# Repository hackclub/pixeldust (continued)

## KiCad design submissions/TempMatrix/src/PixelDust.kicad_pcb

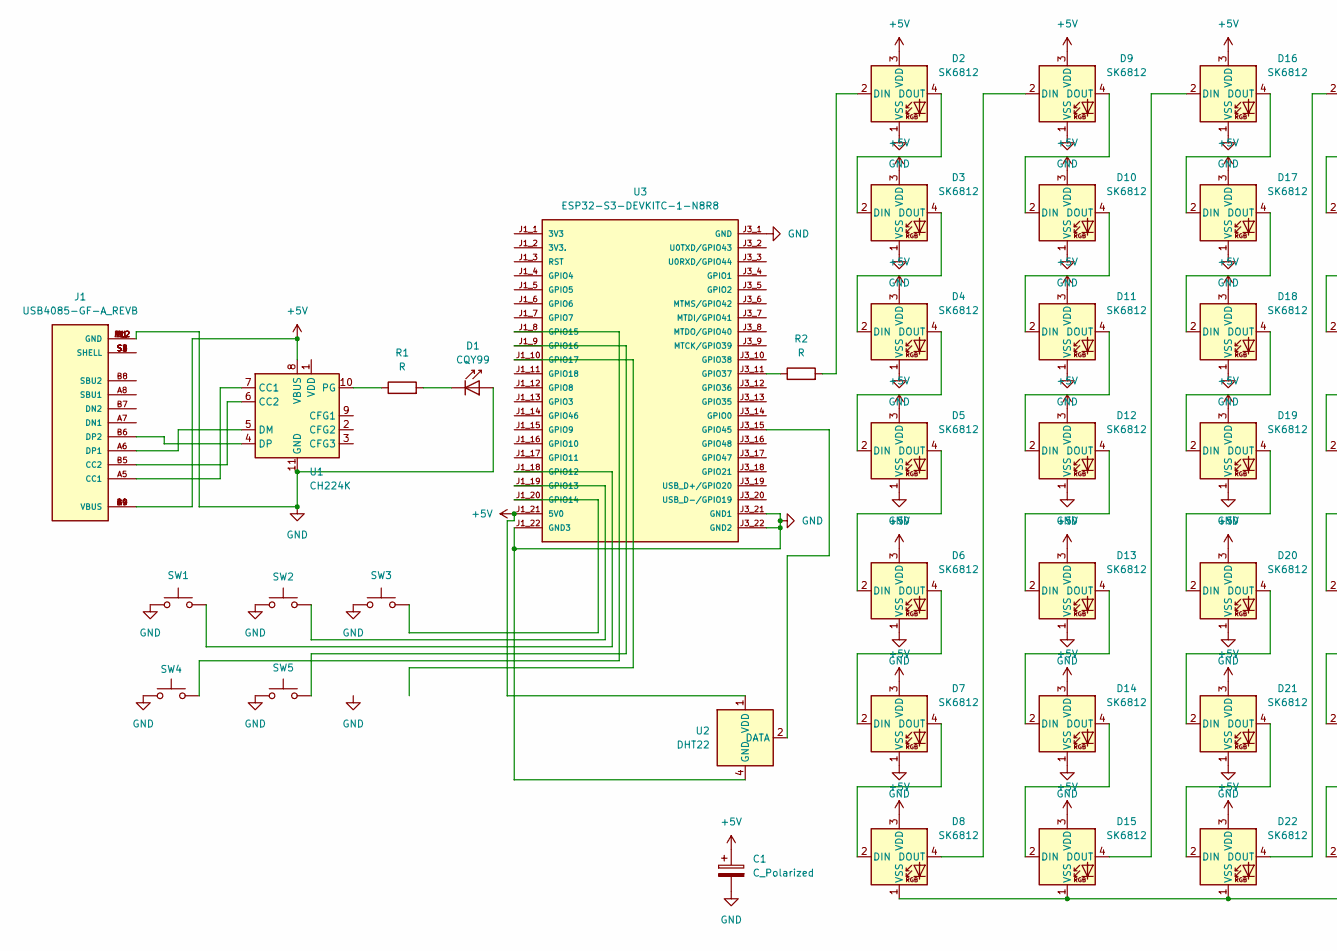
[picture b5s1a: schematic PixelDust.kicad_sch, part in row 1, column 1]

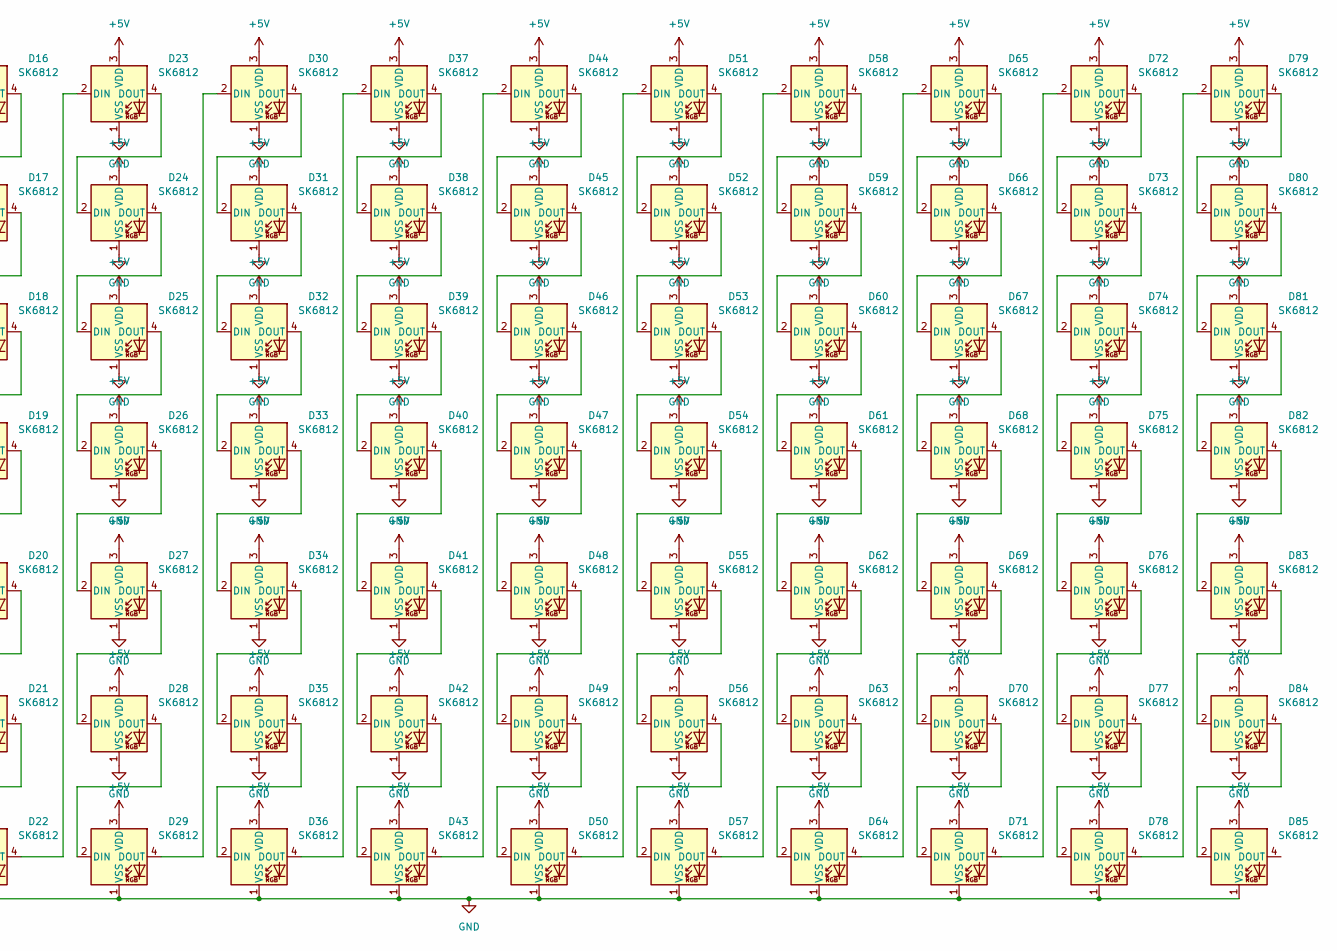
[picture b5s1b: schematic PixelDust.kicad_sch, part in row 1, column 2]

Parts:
C1: C_Polarized; CP_Radial_D10.0mm_P3.50mm
D1: CQY99; LED_D5.0mm_IRGrey
D2, D3, D4, D5, D6, D7, D8, D9, D10, D11, D12, D13, D14, D15, D16, D17, D18, D19, D20, D21, D22, D23, D24, D25, D26, D27, D28, D29, D30, D31, D32, D33, D34, D35, D36, D37, D38, D39, D40, D41, D42, D43, D44, D45, D46, D47, D48, D49, D50, D51, D52, D53, D54, D55, D56, D57, D58, D59, D60, D61, D62, D63, D64, D65, D66, D67, D68, D69, D70, D71, D72, D73, D74, D75, D76, D77, D78, D79, D80, D81, D82, D83, D84, D85: SK6812; LED_SK6812_PLCC4_5.0x5.0mm_P3.2mm
J1: USB4085-GF-A_REVB; GCT_USB4085-GF-A_REVB; PARTREV B; DigiKey_Part_Number 2073-USB4085-GF-ATR-ND
R1: R; R_Axial_DIN0207_L6.3mm_D2.5mm_P7.62mm_Horizontal
R2: R; R_Axial_DIN0207_L6.3mm_D2.5mm_P10.16mm_Horizontal
SW1, SW2, SW3, SW4, SW5: SW_Push; SW_Cherry_MX_PCB_1.00u
U1: CH224K; SSOP-10-1EP_3.9x4.9mm_P1mm_EP2.1x3.3mm
U2: DHT22; Aosong_DHT11_5.5x12.0_P2.54mm
U3: ESP32-S3-DEVKITC-1-N8R8; DigiKey_Part_Number 1965-ESP32-S3-DEVKITC-1-N8R8-ND

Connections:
+5V: C1.1, D2.3 (VDD), D3.3 (VDD), D4.3 (VDD), D5.3 (VDD), D6.3 (VDD), D7.3 (VDD), D8.3 (VDD), D9.3 (VDD), D10.3 (VDD), D11.3 (VDD), D12.3 (VDD), D13.3 (VDD), D14.3 (VDD), D15.3 (VDD), D16.3 (VDD), D17.3 (VDD), D18.3 (VDD), D19.3 (VDD), D20.3 (VDD), D21.3 (VDD), D22.3 (VDD), D23.3 (VDD), D24.3 (VDD), D25.3 (VDD), D26.3 (VDD), D27.3 (VDD), D28.3 (VDD), D29.3 (VDD), D30.3 (VDD), D31.3 (VDD), D32.3 (VDD), D33.3 (VDD), D34.3 (VDD), D35.3 (VDD), D36.3 (VDD), D37.3 (VDD), D38.3 (VDD), D39.3 (VDD), D40.3 (VDD), D41.3 (VDD), D42.3 (VDD), D43.3 (VDD), D44.3 (VDD), D45.3 (VDD), D46.3 (VDD), D47.3 (VDD), D48.3 (VDD), D49.3 (VDD), D50.3 (VDD), D51.3 (VDD), D52.3 (VDD), D53.3 (VDD), D54.3 (VDD), D55.3 (VDD), D56.3 (VDD), D57.3 (VDD), D58.3 (VDD), D59.3 (VDD), D60.3 (VDD), D61.3 (VDD), D62.3 (VDD), D63.3 (VDD), D64.3 (VDD), D65.3 (VDD), D66.3 (VDD), D67.3 (VDD), D68.3 (VDD), D69.3 (VDD), D70.3 (VDD), D71.3 (VDD), D72.3 (VDD), D73.3 (VDD), D74.3 (VDD), D75.3 (VDD), D76.3 (VDD), D77.3 (VDD), D78.3 (VDD), D79.3 (VDD), D80.3 (VDD), D81.3 (VDD), D82.3 (VDD), D83.3 (VDD), D84.3 (VDD), D85.3 (VDD), J1.A4 (VBUS), J1.A9 (VBUS), J1.B4 (VBUS), J1.B9 (VBUS), U1.8 (VBUS), U2.1 (VDD), U3.J1_21 (5V0)
GND: C1.2, D1.2 (A), D2.1 (VSS), D3.1 (VSS), D4.1 (VSS), D5.1 (VSS), D6.1 (VSS), D7.1 (VSS), D8.1 (VSS), D9.1 (VSS), D10.1 (VSS), D11.1 (VSS), D12.1 (VSS), D13.1 (VSS), D14.1 (VSS), D15.1 (VSS), D16.1 (VSS), D17.1 (VSS), D18.1 (VSS), D19.1 (VSS), D20.1 (VSS), D21.1 (VSS), D22.1 (VSS), D23.1 (VSS), D24.1 (VSS), D25.1 (VSS), D26.1 (VSS), D27.1 (VSS), D28.1 (VSS), D29.1 (VSS), D30.1 (VSS), D31.1 (VSS), D32.1 (VSS), D33.1 (VSS), D34.1 (VSS), D35.1 (VSS), D36.1 (VSS), D37.1 (VSS), D38.1 (VSS), D39.1 (VSS), D40.1 (VSS), D41.1 (VSS), D42.1 (VSS), D43.1 (VSS), D44.1 (VSS), D45.1 (VSS), D46.1 (VSS), D47.1 (VSS), D48.1 (VSS), D49.1 (VSS), D50.1 (VSS), D51.1 (VSS), D52.1 (VSS), D53.1 (VSS), D54.1 (VSS), D55.1 (VSS), D56.1 (VSS), D57.1 (VSS), D58.1 (VSS), D59.1 (VSS), D60.1 (VSS), D61.1 (VSS), D62.1 (VSS), D63.1 (VSS), D64.1 (VSS), D65.1 (VSS), D66.1 (VSS), D67.1 (VSS), D68.1 (VSS), D69.1 (VSS), D70.1 (VSS), D71.1 (VSS), D72.1 (VSS), D73.1 (VSS), D74.1 (VSS), D75.1 (VSS), D76.1 (VSS), D77.1 (VSS), D78.1 (VSS), D79.1 (VSS), D80.1 (VSS), D81.1 (VSS), D82.1 (VSS), D83.1 (VSS), D84.1 (VSS), D85.1 (VSS), J1.A1 (GND), J1.A12 (GND), J1.B1 (GND), J1.B12 (GND), SW1.1, SW2.1, SW3.1, SW4.1, SW5.1, U1.11 (GND), U2.4 (GND), U3.J1_22 (GND3), U3.J3_1 (GND), U3.J3_21 (GND1), U3.J3_22 (GND2)
unnamed: D1.1 (K), R1.2
unnamed: D2.2 (DIN), R2.2
unnamed: D2.4 (DOUT), D3.2 (DIN)
unnamed: D3.4 (DOUT), D4.2 (DIN)
unnamed: D4.4 (DOUT), D5.2 (DIN)
unnamed: D5.4 (DOUT), D6.2 (DIN)
unnamed: D6.4 (DOUT), D7.2 (DIN)
unnamed: D7.4 (DOUT), D8.2 (DIN)
unnamed: D8.4 (DOUT), D9.2 (DIN)
unnamed: D9.4 (DOUT), D10.2 (DIN)
unnamed: D10.4 (DOUT), D11.2 (DIN)
unnamed: D11.4 (DOUT), D12.2 (DIN)
unnamed: D12.4 (DOUT), D13.2 (DIN)
unnamed: D13.4 (DOUT), D14.2 (DIN)
unnamed: D14.4 (DOUT), D15.2 (DIN)
unnamed: D15.4 (DOUT), D16.2 (DIN)
unnamed: D16.4 (DOUT), D17.2 (DIN)
unnamed: D17.4 (DOUT), D18.2 (DIN)
unnamed: D18.4 (DOUT), D19.2 (DIN)
unnamed: D19.4 (DOUT), D20.2 (DIN)
unnamed: D20.4 (DOUT), D21.2 (DIN)
unnamed: D21.4 (DOUT), D22.2 (DIN)
unnamed: D22.4 (DOUT), D23.2 (DIN)
unnamed: D23.4 (DOUT), D24.2 (DIN)
unnamed: D24.4 (DOUT), D25.2 (DIN)
unnamed: D25.4 (DOUT), D26.2 (DIN)
unnamed: D26.4 (DOUT), D27.2 (DIN)
unnamed: D27.4 (DOUT), D28.2 (DIN)
unnamed: D28.4 (DOUT), D29.2 (DIN)
unnamed: D29.4 (DOUT), D30.2 (DIN)
unnamed: D30.4 (DOUT), D31.2 (DIN)
unnamed: D31.4 (DOUT), D32.2 (DIN)
unnamed: D32.4 (DOUT), D33.2 (DIN)
unnamed: D33.4 (DOUT), D34.2 (DIN)
unnamed: D34.4 (DOUT), D35.2 (DIN)
unnamed: D35.4 (DOUT), D36.2 (DIN)
unnamed: D36.4 (DOUT), D37.2 (DIN)
unnamed: D37.4 (DOUT), D38.2 (DIN)
unnamed: D38.4 (DOUT), D39.2 (DIN)
unnamed: D39.4 (DOUT), D40.2 (DIN)
unnamed: D40.4 (DOUT), D41.2 (DIN)
unnamed: D41.4 (DOUT), D42.2 (DIN)
unnamed: D42.4 (DOUT), D43.2 (DIN)
unnamed: D43.4 (DOUT), D44.2 (DIN)
unnamed: D44.4 (DOUT), D45.2 (DIN)
unnamed: D45.4 (DOUT), D46.2 (DIN)
unnamed: D46.4 (DOUT), D47.2 (DIN)
unnamed: D47.4 (DOUT), D48.2 (DIN)
unnamed: D48.4 (DOUT), D49.2 (DIN)
unnamed: D49.4 (DOUT), D50.2 (DIN)
unnamed: D50.4 (DOUT), D51.2 (DIN)
unnamed: D51.4 (DOUT), D52.2 (DIN)
unnamed: D52.4 (DOUT), D53.2 (DIN)
unnamed: D53.4 (DOUT), D54.2 (DIN)
unnamed: D54.4 (DOUT), D55.2 (DIN)
unnamed: D55.4 (DOUT), D56.2 (DIN)
unnamed: D56.4 (DOUT), D57.2 (DIN)
unnamed: D57.4 (DOUT), D58.2 (DIN)
unnamed: D58.4 (DOUT), D59.2 (DIN)
unnamed: D59.4 (DOUT), D60.2 (DIN)
unnamed: D60.4 (DOUT), D61.2 (DIN)
unnamed: D61.4 (DOUT), D62.2 (DIN)
unnamed: D62.4 (DOUT), D63.2 (DIN)
unnamed: D63.4 (DOUT), D64.2 (DIN)
unnamed: D64.4 (DOUT), D65.2 (DIN)
unnamed: D65.4 (DOUT), D66.2 (DIN)
unnamed: D66.4 (DOUT), D67.2 (DIN)
unnamed: D67.4 (DOUT), D68.2 (DIN)
unnamed: D68.4 (DOUT), D69.2 (DIN)
unnamed: D69.4 (DOUT), D70.2 (DIN)
unnamed: D70.4 (DOUT), D71.2 (DIN)
unnamed: D71.4 (DOUT), D72.2 (DIN)
unnamed: D72.4 (DOUT), D73.2 (DIN)
unnamed: D73.4 (DOUT), D74.2 (DIN)
unnamed: D74.4 (DOUT), D75.2 (DIN)
unnamed: D75.4 (DOUT), D76.2 (DIN)
unnamed: D76.4 (DOUT), D77.2 (DIN)
unnamed: D77.4 (DOUT), D78.2 (DIN)
unnamed: D78.4 (DOUT), D79.2 (DIN)
unnamed: D79.4 (DOUT), D80.2 (DIN)
unnamed: D80.4 (DOUT), D81.2 (DIN)
unnamed: D81.4 (DOUT), D82.2 (DIN)
unnamed: D82.4 (DOUT), D83.2 (DIN)
unnamed: D83.4 (DOUT), D84.2 (DIN)
unnamed: D84.4 (DOUT), D85.2 (DIN)
unnamed: J1.A5 (CC1), U1.7 (CC1)
unnamed: J1.B5 (CC2), U1.6 (CC2)
unnamed: J1.A6 (DP1), U1.5 (DM)
unnamed: J1.B6 (DP2), U1.4 (DP)
unnamed: J1.S1 (SHELL), J1.S2 (SHELL), J1.S3 (SHELL), J1.S4 (SHELL)
unnamed: R1.1, U1.10 (PG)
unnamed: U2.2 (DATA), U3.J3_15 (GPIO45)
unnamed: SW1.2, U3.J1_18 (GPIO12)
unnamed: SW2.2, U3.J1_19 (GPIO13)
unnamed: SW3.2, U3.J1_20 (GPIO14)
unnamed: SW4.2, U3.J1_8 (GPIO15)
unnamed: SW5.2, U3.J1_9 (GPIO16)
unnamed: R2.1, U3.J3_11 (GPIO37)

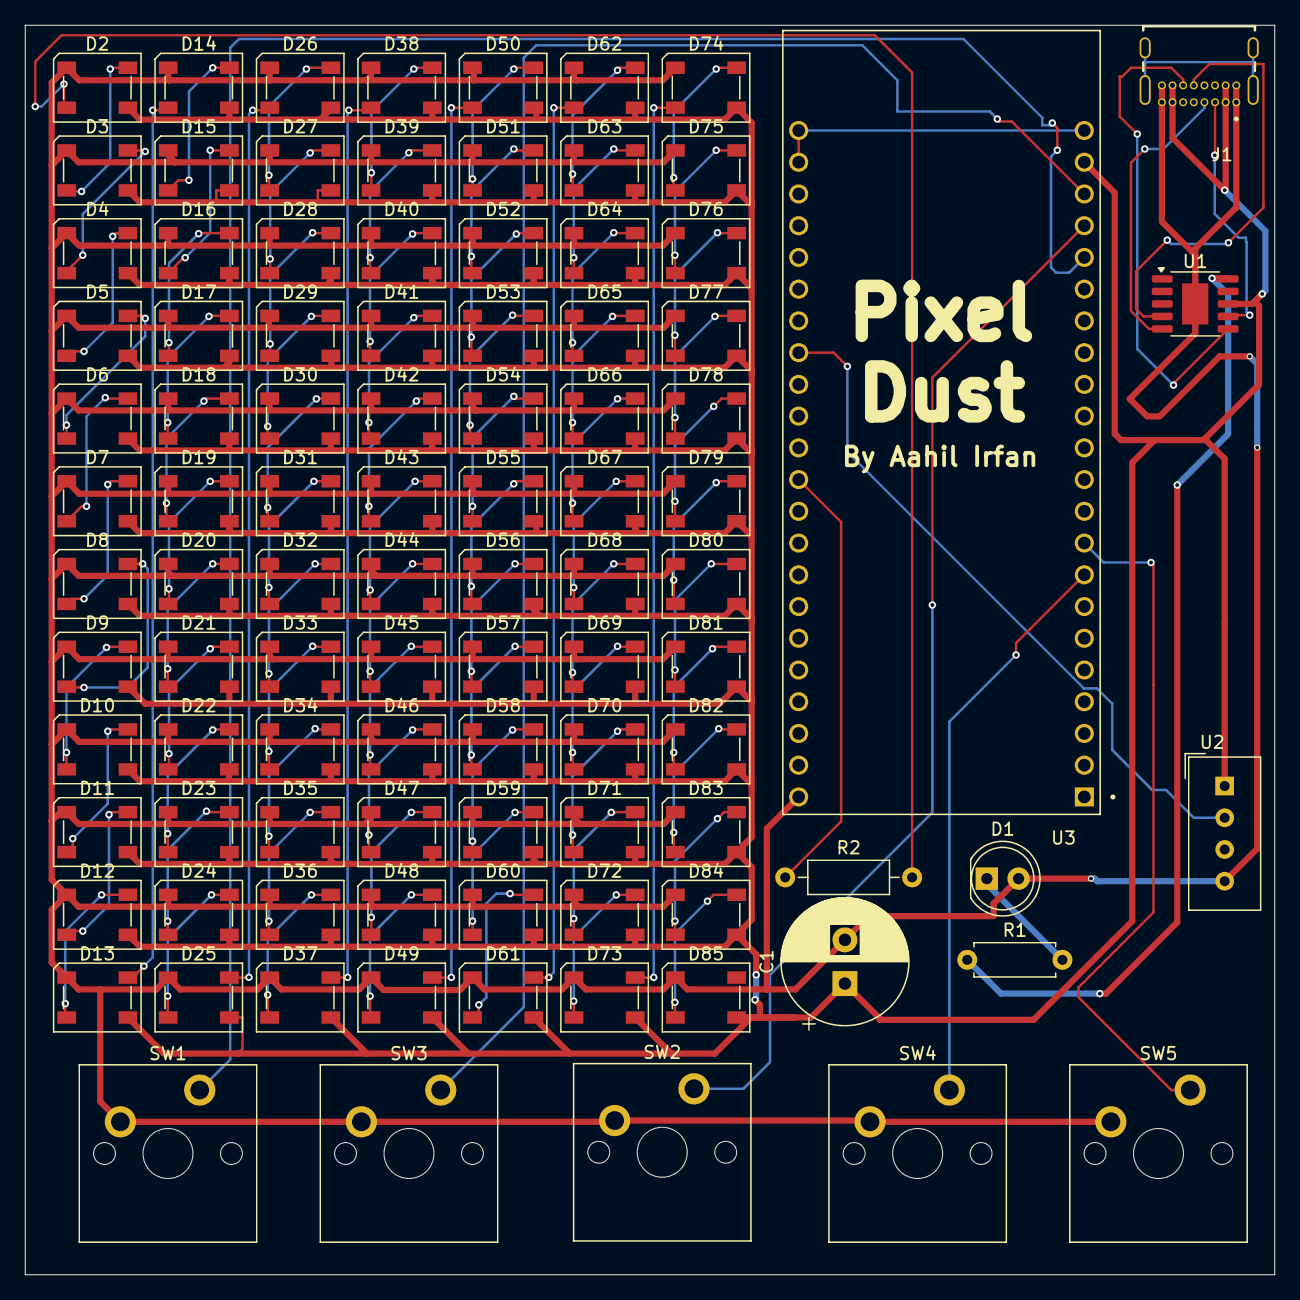
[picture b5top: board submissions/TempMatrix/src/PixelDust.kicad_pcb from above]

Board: 2 copper layers, 100.0 x 100.0 mm, 97 parts (0 on the bottom side), 100 nets.

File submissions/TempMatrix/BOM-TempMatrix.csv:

Item,Quantity,Notes
 ESP32-S3-DEVKITC-1-N8R8,1,Can I get an extra pls? I tend to fry things
CH224K ,1,PD Controller IC
0305-2-15-80-47-80-10-0,10,Switches Hotswap Sockets
100uF Capacitor,1,Would be great to get extras bc I loose them or they smoke up
SK6812 LEDs,84,Can you solder them please?
330ohm Resistor,1,For data pin
220ohm Resistor,1,For LED
USB4085-GF-A_REVB,1,Type C port - Can you solder this too?
 Red LED Through hole,A few bc i loose them (if possible otherwise 1),Power Good LED
DHT22 sensor,1,Temperature Sensor
Cherry MX Speed Silver,5,Keys to interact and for my game
Soldering Iron,1,If possible could you send a kit with a helping hand too?
Some stickerrssss,A few,If possible bc why not? lol

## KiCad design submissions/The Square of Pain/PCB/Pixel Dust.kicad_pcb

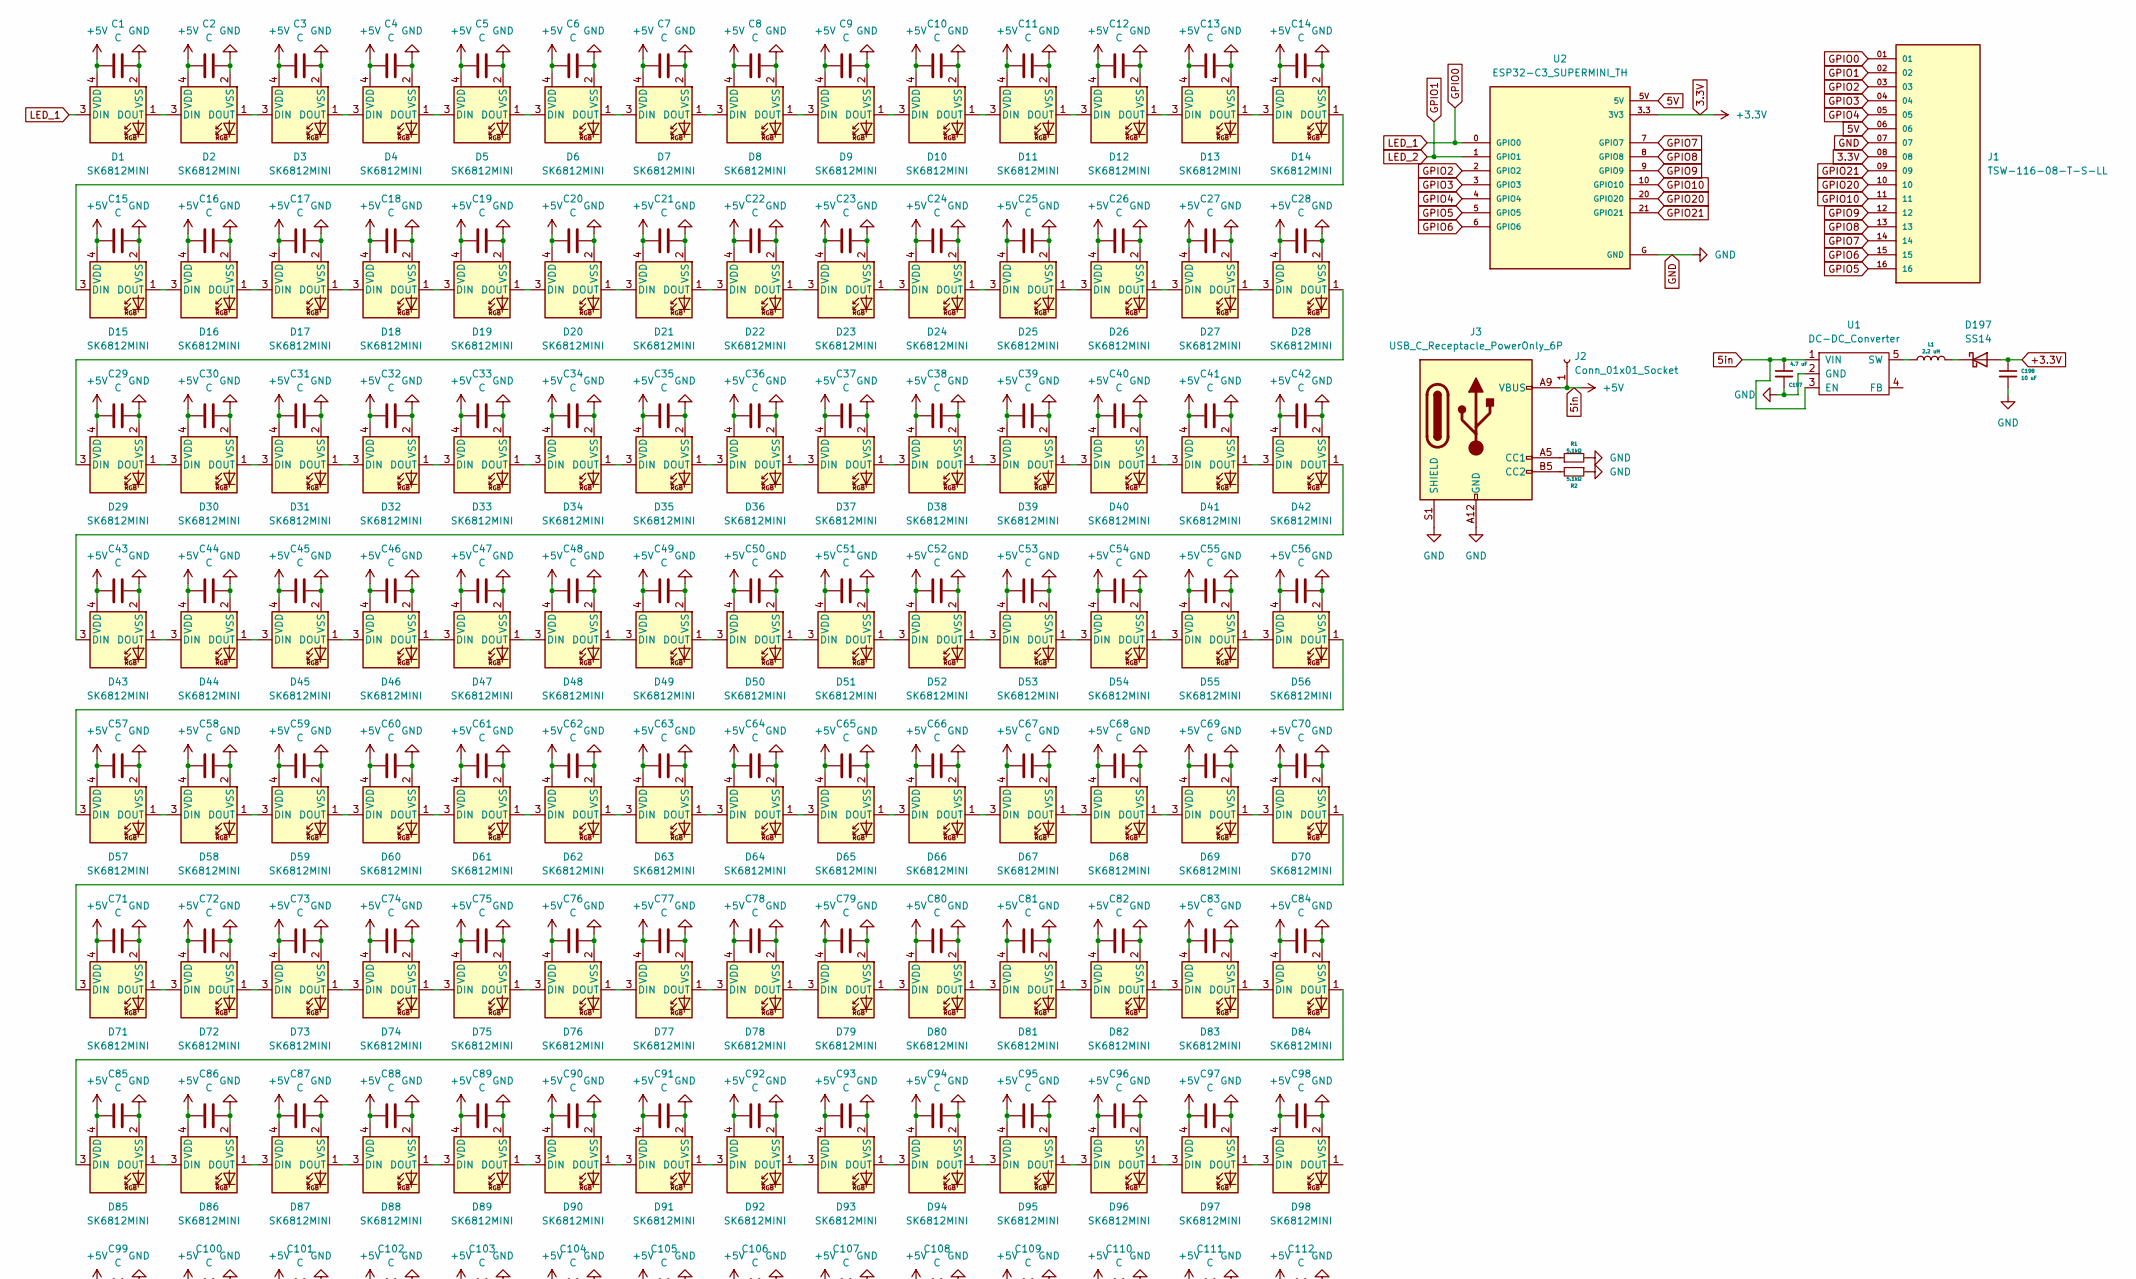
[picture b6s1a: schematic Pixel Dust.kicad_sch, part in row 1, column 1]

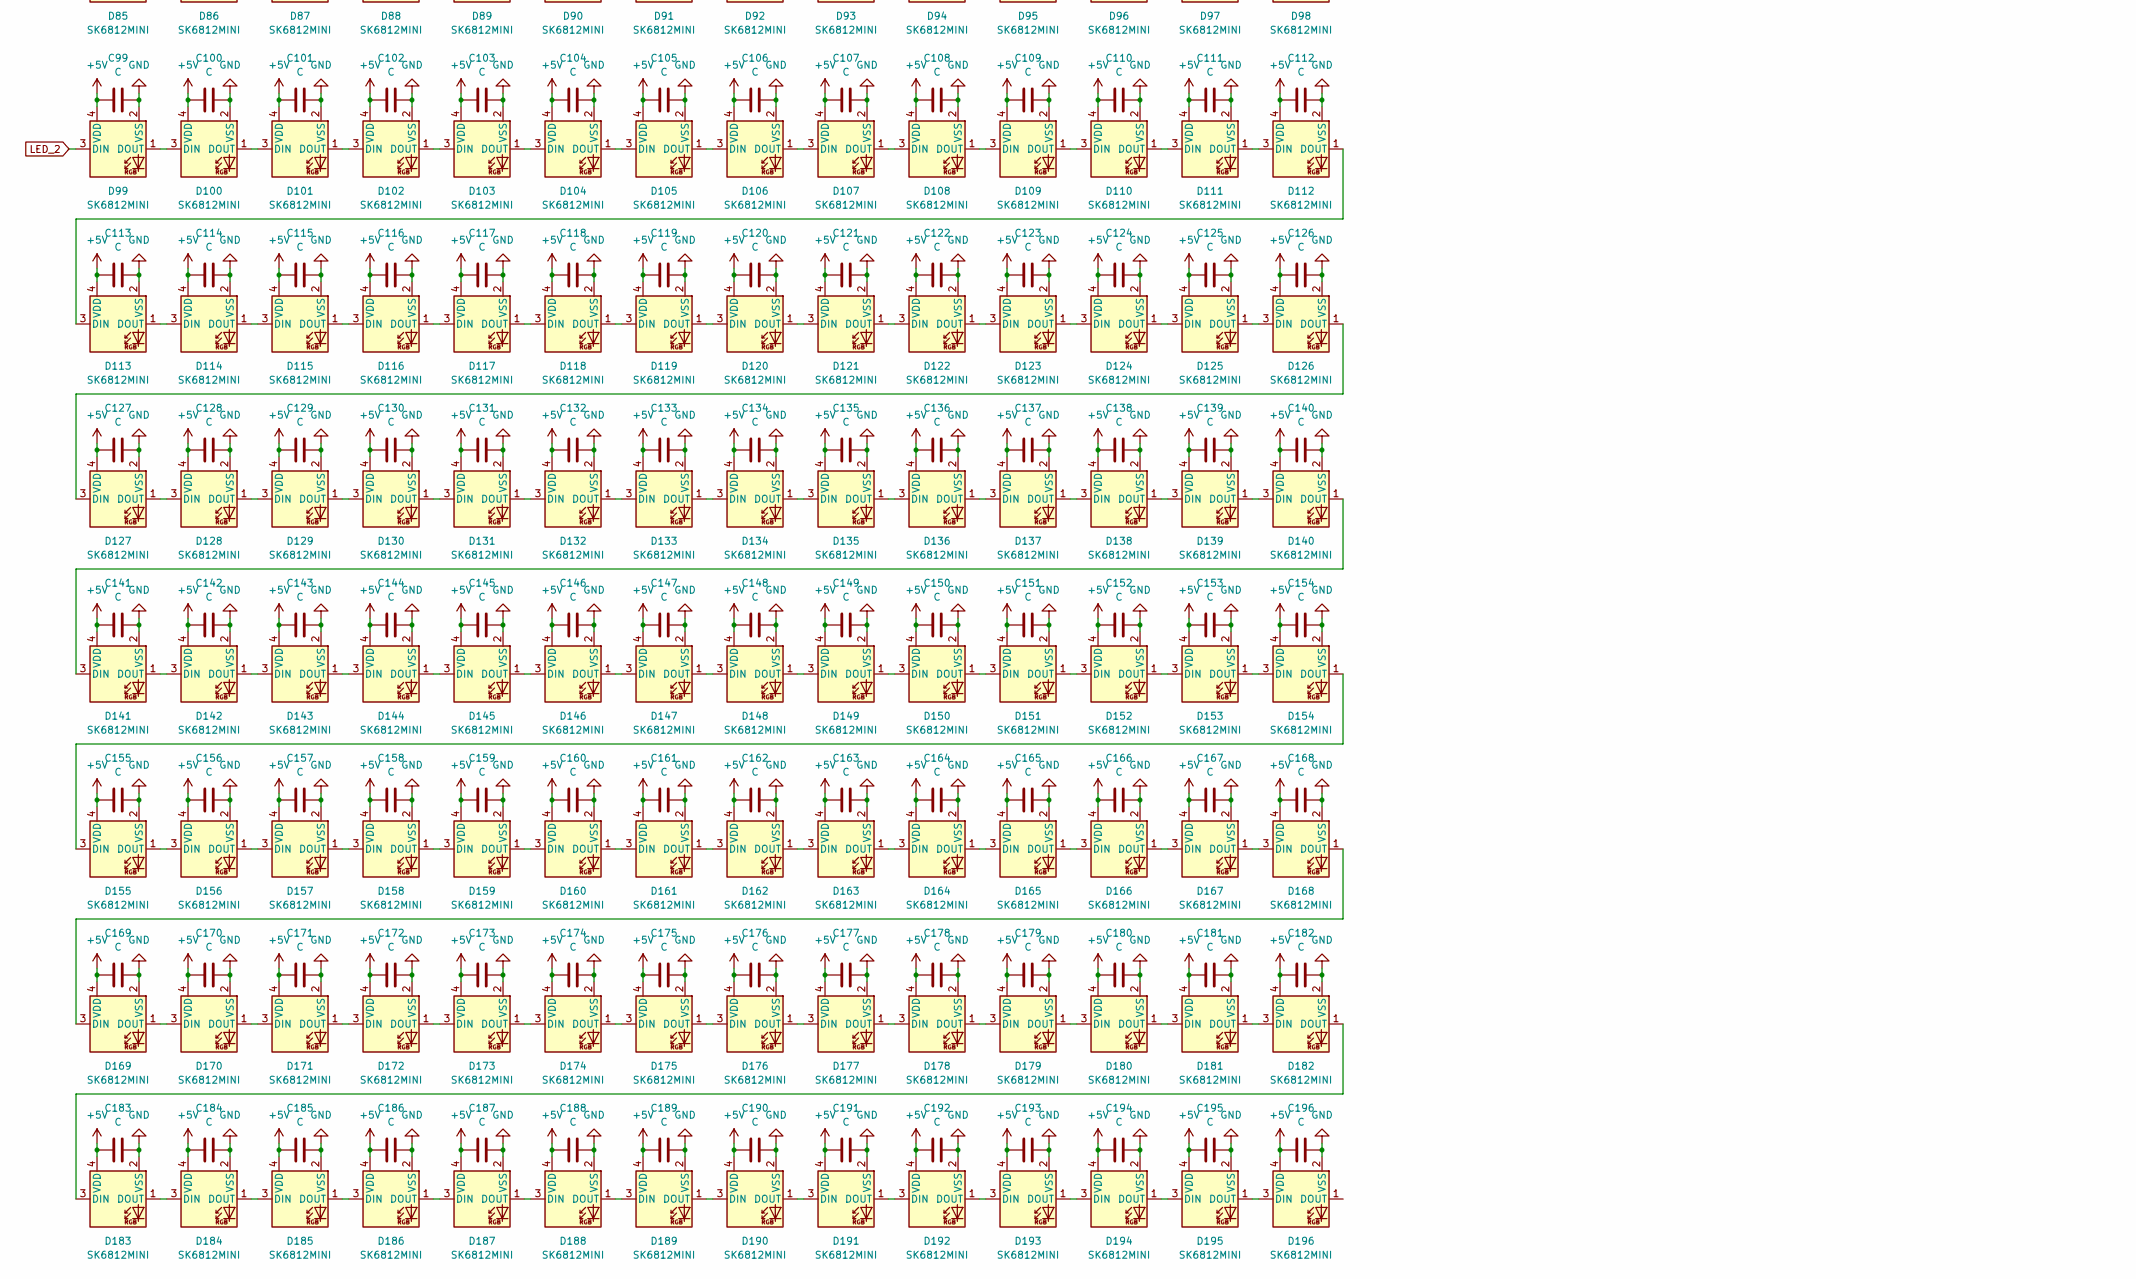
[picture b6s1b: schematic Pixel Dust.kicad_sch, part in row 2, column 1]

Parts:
C1, C2, C3, C4, C5, C6, C7, C8, C9, C10, C11, C12, C13, C14, C15, C16, C17, C18, C19, C20, C21, C22, C23, C24, C25, C26, C27, C28, C29, C30, C31, C32, C33, C34, C35, C36, C37, C38, C39, C40, C41, C42, C43, C44, C45, C46, C47, C48, C49, C50, C51, C52, C53, C54, C55, C56, C57, C58, C59, C60, C61, C62, C63, C64, C65, C66, C67, C68, C69, C70, C71, C72, C73, C74, C75, C76, C77, C78, C79, C80, C81, C82, C83, C84, C85, C86, C87, C88, C89, C90, C91, C92, C93, C94, C95, C96, C97, C98, C99, C100, C101, C102, C103, C104, C105, C106, C107, C108, C109, C110, C111, C112, C113, C114, C115, C116, C117, C118, C119, C120, C121, C122, C123, C124, C125, C126, C127, C128, C129, C130, C131, C132, C133, C134, C135, C136, C137, C138, C139, C140, C141, C142, C143, C144, C145, C146, C147, C148, C149, C150, C151, C152, C153, C154, C155, C156, C157, C158, C159, C160, C161, C162, C163, C164, C165, C166, C167, C168, C169, C170, C171, C172, C173, C174, C175, C176, C177, C178, C179, C180, C181, C182, C183, C184, C185, C186, C187, C188, C189, C190, C191, C192, C193, C194, C195, C196: C; C_0805_2012Metric_Pad1.18x1.45mm_HandSolder
C197: 4.7 uF; CAPC2012X140N
C198: 10 uF; CAPC2012X135N
D1, D2, D3, D4, D5, D6, D7, D8, D9, D10, D11, D12, D13, D14, D15, D16, D17, D18, D19, D20, D21, D22, D23, D24, D25, D26, D27, D28, D29, D30, D31, D32, D33, D34, D35, D36, D37, D38, D39, D40, D41, D42, D43, D44, D45, D46, D47, D48, D49, D50, D51, D52, D53, D54, D55, D56, D57, D58, D59, D60, D61, D62, D63, D64, D65, D66, D67, D68, D69, D70, D71, D72, D73, D74, D75, D76, D77, D78, D79, D80, D81, D82, D83, D84, D85, D86, D87, D88, D89, D90, D91, D92, D93, D94, D95, D96, D97, D98, D99, D100, D101, D102, D103, D104, D105, D106, D107, D108, D109, D110, D111, D112, D113, D114, D115, D116, D117, D118, D119, D120, D121, D122, D123, D124, D125, D126, D127, D128, D129, D130, D131, D132, D133, D134, D135, D136, D137, D138, D139, D140, D141, D142, D143, D144, D145, D146, D147, D148, D149, D150, D151, D152, D153, D154, D155, D156, D157, D158, D159, D160, D161, D162, D163, D164, D165, D166, D167, D168, D169, D170, D171, D172, D173, D174, D175, D176, D177, D178, D179, D180, D181, D182, D183, D184, D185, D186, D187, D188, D189, D190, D191, D192, D193, D194, D195, D196: SK6812MINI; SK6812MINI-E
D197: SS14; D_SMA
J1: TSW-116-08-T-S-LL; SAMTEC_TSW-116-08-T-S-LL; PARTREV R
J2: Conn_01x01_Socket; PinSocket_1x01_P1.27mm_Vertical
J3: USB_C_Receptacle_PowerOnly_6P; SAMESKY_UJC-H-G-SMT-2-P6-TR
L1: 2.2 uH; CDRH2D14NP-2R2NC
R1, R2: 5.1kΩ; R_0603_1608Metric_Pad0.98x0.95mm_HandSolder
U1: DC-DC_Converter
U2: ESP32-C3_SUPERMINI_TH; MODULE_ESP32-C3_SUPERMINI

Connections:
5V: J1.06, U2.5V
5in: C1.1, C2.1, C3.1, C4.1, C5.1, C6.1, C7.1, C8.1, C9.1, C10.1, C11.1, C12.1, C13.1, C14.1, C15.1, C16.1, C17.1, C18.1, C19.1, C20.1, C21.1, C22.1, C23.1, C24.1, C25.1, C26.1, C27.1, C28.1, C29.1, C30.1, C31.1, C32.1, C33.1, C34.1, C35.1, C36.1, C37.1, C38.1, C39.1, C40.1, C41.1, C42.1, C43.1, C44.1, C45.1, C46.1, C47.1, C48.1, C49.1, C50.1, C51.1, C52.1, C53.1, C54.1, C55.1, C56.1, C57.1, C58.1, C59.1, C60.1, C61.1, C62.1, C63.1, C64.1, C65.1, C66.1, C67.1, C68.1, C69.1, C70.1, C71.1, C72.1, C73.1, C74.1, C75.1, C76.1, C77.1, C78.1, C79.1, C80.1, C81.1, C82.1, C83.1, C84.1, C85.1, C86.1, C87.1, C88.1, C89.1, C90.1, C91.1, C92.1, C93.1, C94.1, C95.1, C96.1, C97.1, C98.1, C99.1, C100.1, C101.1, C102.1, C103.1, C104.1, C105.1, C106.1, C107.1, C108.1, C109.1, C110.1, C111.1, C112.1, C113.1, C114.1, C115.1, C116.1, C117.1, C118.1, C119.1, C120.1, C121.1, C122.1, C123.1, C124.1, C125.1, C126.1, C127.1, C128.1, C129.1, C130.1, C131.1, C132.1, C133.1, C134.1, C135.1, C136.1, C137.1, C138.1, C139.1, C140.1, C141.1, C142.1, C143.1, C144.1, C145.1, C146.1, C147.1, C148.1, C149.1, C150.1, C151.1, C152.1, C153.1, C154.1, C155.1, C156.1, C157.1, C158.1, C159.1, C160.1, C161.1, C162.1, C163.1, C164.1, C165.1, C166.1, C167.1, C168.1, C169.1, C170.1, C171.1, C172.1, C173.1, C174.1, C175.1, C176.1, C177.1, C178.1, C179.1, C180.1, C181.1, C182.1, C183.1, C184.1, C185.1, C186.1, C187.1, C188.1, C189.1, C190.1, C191.1, C192.1, C193.1, C194.1, C195.1, C196.1, C197.1, D1.4 (VDD), D2.4 (VDD), D3.4 (VDD), D4.4 (VDD), D5.4 (VDD), D6.4 (VDD), D7.4 (VDD), D8.4 (VDD), D9.4 (VDD), D10.4 (VDD), D11.4 (VDD), D12.4 (VDD), D13.4 (VDD), D14.4 (VDD), D15.4 (VDD), D16.4 (VDD), D17.4 (VDD), D18.4 (VDD), D19.4 (VDD), D20.4 (VDD), D21.4 (VDD), D22.4 (VDD), D23.4 (VDD), D24.4 (VDD), D25.4 (VDD), D26.4 (VDD), D27.4 (VDD), D28.4 (VDD), D29.4 (VDD), D30.4 (VDD), D31.4 (VDD), D32.4 (VDD), D33.4 (VDD), D34.4 (VDD), D35.4 (VDD), D36.4 (VDD), D37.4 (VDD), D38.4 (VDD), D39.4 (VDD), D40.4 (VDD), D41.4 (VDD), D42.4 (VDD), D43.4 (VDD), D44.4 (VDD), D45.4 (VDD), D46.4 (VDD), D47.4 (VDD), D48.4 (VDD), D49.4 (VDD), D50.4 (VDD), D51.4 (VDD), D52.4 (VDD), D53.4 (VDD), D54.4 (VDD), D55.4 (VDD), D56.4 (VDD), D57.4 (VDD), D58.4 (VDD), D59.4 (VDD), D60.4 (VDD), D61.4 (VDD), D62.4 (VDD), D63.4 (VDD), D64.4 (VDD), D65.4 (VDD), D66.4 (VDD), D67.4 (VDD), D68.4 (VDD), D69.4 (VDD), D70.4 (VDD), D71.4 (VDD), D72.4 (VDD), D73.4 (VDD), D74.4 (VDD), D75.4 (VDD), D76.4 (VDD), D77.4 (VDD), D78.4 (VDD), D79.4 (VDD), D80.4 (VDD), D81.4 (VDD), D82.4 (VDD), D83.4 (VDD), D84.4 (VDD), D85.4 (VDD), D86.4 (VDD), D87.4 (VDD), D88.4 (VDD), D89.4 (VDD), D90.4 (VDD), D91.4 (VDD), D92.4 (VDD), D93.4 (VDD), D94.4 (VDD), D95.4 (VDD), D96.4 (VDD), D97.4 (VDD), D98.4 (VDD), D99.4 (VDD), D100.4 (VDD), D101.4 (VDD), D102.4 (VDD), D103.4 (VDD), D104.4 (VDD), D105.4 (VDD), D106.4 (VDD), D107.4 (VDD), D108.4 (VDD), D109.4 (VDD), D110.4 (VDD), D111.4 (VDD), D112.4 (VDD), D113.4 (VDD), D114.4 (VDD), D115.4 (VDD), D116.4 (VDD), D117.4 (VDD), D118.4 (VDD), D119.4 (VDD), D120.4 (VDD), D121.4 (VDD), D122.4 (VDD), D123.4 (VDD), D124.4 (VDD), D125.4 (VDD), D126.4 (VDD), D127.4 (VDD), D128.4 (VDD), D129.4 (VDD), D130.4 (VDD), D131.4 (VDD), D132.4 (VDD), D133.4 (VDD), D134.4 (VDD), D135.4 (VDD), D136.4 (VDD), D137.4 (VDD), D138.4 (VDD), D139.4 (VDD), D140.4 (VDD), D141.4 (VDD), D142.4 (VDD), D143.4 (VDD), D144.4 (VDD), D145.4 (VDD), D146.4 (VDD), D147.4 (VDD), D148.4 (VDD), D149.4 (VDD), D150.4 (VDD), D151.4 (VDD), D152.4 (VDD), D153.4 (VDD), D154.4 (VDD), D155.4 (VDD), D156.4 (VDD), D157.4 (VDD), D158.4 (VDD), D159.4 (VDD), D160.4 (VDD), D161.4 (VDD), D162.4 (VDD), D163.4 (VDD), D164.4 (VDD), D165.4 (VDD), D166.4 (VDD), D167.4 (VDD), D168.4 (VDD), D169.4 (VDD), D170.4 (VDD), D171.4 (VDD), D172.4 (VDD), D173.4 (VDD), D174.4 (VDD), D175.4 (VDD), D176.4 (VDD), D177.4 (VDD), D178.4 (VDD), D179.4 (VDD)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
+3.3V: C198.1, D197.2 (A), J1.08, U2.3.3 (3V3)
GND: C1.2, C2.2, C3.2, C4.2, C5.2, C6.2, C7.2, C8.2, C9.2, C10.2, C11.2, C12.2, C13.2, C14.2, C15.2, C16.2, C17.2, C18.2, C19.2, C20.2, C21.2, C22.2, C23.2, C24.2, C25.2, C26.2, C27.2, C28.2, C29.2, C30.2, C31.2, C32.2, C33.2, C34.2, C35.2, C36.2, C37.2, C38.2, C39.2, C40.2, C41.2, C42.2, C43.2, C44.2, C45.2, C46.2, C47.2, C48.2, C49.2, C50.2, C51.2, C52.2, C53.2, C54.2, C55.2, C56.2, C57.2, C58.2, C59.2, C60.2, C61.2, C62.2, C63.2, C64.2, C65.2, C66.2, C67.2, C68.2, C69.2, C70.2, C71.2, C72.2, C73.2, C74.2, C75.2, C76.2, C77.2, C78.2, C79.2, C80.2, C81.2, C82.2, C83.2, C84.2, C85.2, C86.2, C87.2, C88.2, C89.2, C90.2, C91.2, C92.2, C93.2, C94.2, C95.2, C96.2, C97.2, C98.2, C99.2, C100.2, C101.2, C102.2, C103.2, C104.2, C105.2, C106.2, C107.2, C108.2, C109.2, C110.2, C111.2, C112.2, C113.2, C114.2, C115.2, C116.2, C117.2, C118.2, C119.2, C120.2, C121.2, C122.2, C123.2, C124.2, C125.2, C126.2, C127.2, C128.2, C129.2, C130.2, C131.2, C132.2, C133.2, C134.2, C135.2, C136.2, C137.2, C138.2, C139.2, C140.2, C141.2, C142.2, C143.2, C144.2, C145.2, C146.2, C147.2, C148.2, C149.2, C150.2, C151.2, C152.2, C153.2, C154.2, C155.2, C156.2, C157.2, C158.2, C159.2, C160.2, C161.2, C162.2, C163.2, C164.2, C165.2, C166.2, C167.2, C168.2, C169.2, C170.2, C171.2, C172.2, C173.2, C174.2, C175.2, C176.2, C177.2, C178.2, C179.2, C180.2, C181.2, C182.2, C183.2, C184.2, C185.2, C186.2, C187.2, C188.2, C189.2, C190.2, C191.2, C192.2, C193.2, C194.2, C195.2, C196.2, C197.2, C198.2, D1.2 (VSS), D2.2 (VSS), D3.2 (VSS), D4.2 (VSS), D5.2 (VSS), D6.2 (VSS), D7.2 (VSS), D8.2 (VSS), D9.2 (VSS), D10.2 (VSS), D11.2 (VSS), D12.2 (VSS), D13.2 (VSS), D14.2 (VSS), D15.2 (VSS), D16.2 (VSS), D17.2 (VSS), D18.2 (VSS), D19.2 (VSS), D20.2 (VSS), D21.2 (VSS), D22.2 (VSS), D23.2 (VSS), D24.2 (VSS), D25.2 (VSS), D26.2 (VSS), D27.2 (VSS), D28.2 (VSS), D29.2 (VSS), D30.2 (VSS), D31.2 (VSS), D32.2 (VSS), D33.2 (VSS), D34.2 (VSS), D35.2 (VSS), D36.2 (VSS), D37.2 (VSS), D38.2 (VSS), D39.2 (VSS), D40.2 (VSS), D41.2 (VSS), D42.2 (VSS), D43.2 (VSS), D44.2 (VSS), D45.2 (VSS), D46.2 (VSS), D47.2 (VSS), D48.2 (VSS), D49.2 (VSS), D50.2 (VSS), D51.2 (VSS), D52.2 (VSS), D53.2 (VSS), D54.2 (VSS), D55.2 (VSS), D56.2 (VSS), D57.2 (VSS), D58.2 (VSS), D59.2 (VSS), D60.2 (VSS), D61.2 (VSS), D62.2 (VSS), D63.2 (VSS), D64.2 (VSS), D65.2 (VSS), D66.2 (VSS), D67.2 (VSS), D68.2 (VSS), D69.2 (VSS), D70.2 (VSS), D71.2 (VSS), D72.2 (VSS), D73.2 (VSS), D74.2 (VSS), D75.2 (VSS), D76.2 (VSS), D77.2 (VSS), D78.2 (VSS), D79.2 (VSS), D80.2 (VSS), D81.2 (VSS), D82.2 (VSS), D83.2 (VSS), D84.2 (VSS), D85.2 (VSS), D86.2 (VSS), D87.2 (VSS), D88.2 (VSS), D89.2 (VSS), D90.2 (VSS), D91.2 (VSS), D92.2 (VSS), D93.2 (VSS), D94.2 (VSS), D95.2 (VSS), D96.2 (VSS), D97.2 (VSS), D98.2 (VSS), D99.2 (VSS), D100.2 (VSS), D101.2 (VSS), D102.2 (VSS), D103.2 (VSS), D104.2 (VSS), D105.2 (VSS), D106.2 (VSS), D107.2 (VSS), D108.2 (VSS), D109.2 (VSS), D110.2 (VSS), D111.2 (VSS), D112.2 (VSS), D113.2 (VSS), D114.2 (VSS), D115.2 (VSS), D116.2 (VSS), D117.2 (VSS), D118.2 (VSS), D119.2 (VSS), D120.2 (VSS), D121.2 (VSS), D122.2 (VSS), D123.2 (VSS), D124.2 (VSS), D125.2 (VSS), D126.2 (VSS), D127.2 (VSS), D128.2 (VSS), D129.2 (VSS), D130.2 (VSS), D131.2 (VSS), D132.2 (VSS), D133.2 (VSS), D134.2 (VSS), D135.2 (VSS), D136.2 (VSS), D137.2 (VSS), D138.2 (VSS), D139.2 (VSS), D140.2 (VSS), D141.2 (VSS), D142.2 (VSS), D143.2 (VSS), D144.2 (VSS), D145.2 (VSS), D146.2 (VSS), D147.2 (VSS), D148.2 (VSS), D149.2 (VSS), D150.2 (VSS), D151.2 (VSS), D152.2 (VSS), D153.2 (VSS), D154.2 (VSS), D155.2 (VSS), D156.2 (VSS), D157.2 (VSS), D158.2 (VSS), D159.2 (VSS), D160.2 (VSS), D161.2 (VSS), D162.2 (VSS), D163.2 (VSS), D164.2 (VSS), D165.2 (VSS), D166.2 (VSS), D167.2 (VSS), D168.2 (VSS), D169.2 (VSS), D170.2 (VSS), D171.2 (VSS), D172.2 (VSS), D173.2 (VSS), D174.2 (VSS), D175.2 (VSS), D176.2 (VSS), D177.2 (VSS), D178.2 (VSS)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
GPIO0: D1.3 (DIN), J1.01, U2.0 (GPIO0)
GPIO1: D99.3 (DIN), J1.02, U2.1 (GPIO1)
GPIO2: J1.03, U2.2 (GPIO2)
GPIO3: J1.04, U2.3 (GPIO3)
GPIO4: J1.05, U2.4 (GPIO4)
GPIO5: J1.16, U2.5 (GPIO5)
GPIO6: J1.15, U2.6 (GPIO6)
GPIO7: J1.14, U2.7 (GPIO7)
GPIO8: J1.13, U2.8 (GPIO8)
GPIO9: J1.12, U2.9 (GPIO9)
GPIO10: J1.11, U2.10 (GPIO10)
GPIO20: J1.10, U2.20 (GPIO20)
GPIO21: J1.09, U2.21 (GPIO21)
unnamed: D1.1 (DOUT), D2.3 (DIN)
unnamed: D2.1 (DOUT), D3.3 (DIN)
unnamed: D3.1 (DOUT), D4.3 (DIN)
unnamed: D4.1 (DOUT), D5.3 (DIN)
unnamed: D5.1 (DOUT), D6.3 (DIN)
unnamed: D6.1 (DOUT), D7.3 (DIN)
unnamed: D7.1 (DOUT), D8.3 (DIN)
unnamed: D8.1 (DOUT), D9.3 (DIN)
unnamed: D9.1 (DOUT), D10.3 (DIN)
unnamed: D10.1 (DOUT), D11.3 (DIN)
unnamed: D11.1 (DOUT), D12.3 (DIN)
unnamed: D12.1 (DOUT), D13.3 (DIN)
unnamed: D13.1 (DOUT), D14.3 (DIN)
unnamed: D14.1 (DOUT), D15.3 (DIN)
unnamed: D15.1 (DOUT), D16.3 (DIN)
unnamed: D16.1 (DOUT), D17.3 (DIN)
unnamed: D17.1 (DOUT), D18.3 (DIN)
unnamed: D18.1 (DOUT), D19.3 (DIN)
unnamed: D19.1 (DOUT), D20.3 (DIN)
unnamed: D20.1 (DOUT), D21.3 (DIN)
unnamed: D21.1 (DOUT), D22.3 (DIN)
unnamed: D22.1 (DOUT), D23.3 (DIN)
unnamed: D23.1 (DOUT), D24.3 (DIN)
unnamed: D24.1 (DOUT), D25.3 (DIN)
unnamed: D25.1 (DOUT), D26.3 (DIN)
unnamed: D26.1 (DOUT), D27.3 (DIN)
unnamed: D27.1 (DOUT), D28.3 (DIN)
unnamed: D28.1 (DOUT), D29.3 (DIN)
unnamed: D29.1 (DOUT), D30.3 (DIN)
unnamed: D30.1 (DOUT), D31.3 (DIN)
unnamed: D31.1 (DOUT), D32.3 (DIN)
unnamed: D32.1 (DOUT), D33.3 (DIN)
unnamed: D33.1 (DOUT), D34.3 (DIN)
unnamed: D34.1 (DOUT), D35.3 (DIN)
unnamed: D35.1 (DOUT), D36.3 (DIN)
unnamed: D36.1 (DOUT), D37.3 (DIN)
unnamed: D37.1 (DOUT), D38.3 (DIN)
unnamed: D38.1 (DOUT), D39.3 (DIN)
unnamed: D39.1 (DOUT), D40.3 (DIN)
unnamed: D40.1 (DOUT), D41.3 (DIN)
unnamed: D41.1 (DOUT), D42.3 (DIN)
unnamed: D42.1 (DOUT), D43.3 (DIN)
unnamed: D43.1 (DOUT), D44.3 (DIN)
unnamed: D44.1 (DOUT), D45.3 (DIN)
unnamed: D45.1 (DOUT), D46.3 (DIN)
unnamed: D46.1 (DOUT), D47.3 (DIN)
unnamed: D47.1 (DOUT), D48.3 (DIN)
unnamed: D48.1 (DOUT), D49.3 (DIN)
unnamed: D49.1 (DOUT), D50.3 (DIN)
unnamed: D50.1 (DOUT), D51.3 (DIN)
unnamed: D51.1 (DOUT), D52.3 (DIN)
unnamed: D52.1 (DOUT), D53.3 (DIN)
unnamed: D53.1 (DOUT), D54.3 (DIN)
unnamed: D54.1 (DOUT), D55.3 (DIN)
unnamed: D55.1 (DOUT), D56.3 (DIN)
unnamed: D56.1 (DOUT), D57.3 (DIN)
unnamed: D57.1 (DOUT), D58.3 (DIN)
unnamed: D58.1 (DOUT), D59.3 (DIN)
unnamed: D59.1 (DOUT), D60.3 (DIN)
unnamed: D60.1 (DOUT), D61.3 (DIN)
unnamed: D61.1 (DOUT), D62.3 (DIN)
unnamed: D62.1 (DOUT), D63.3 (DIN)
unnamed: D63.1 (DOUT), D64.3 (DIN)
unnamed: D64.1 (DOUT), D65.3 (DIN)
unnamed: D65.1 (DOUT), D66.3 (DIN)
unnamed: D66.1 (DOUT), D67.3 (DIN)
unnamed: D67.1 (DOUT), D68.3 (DIN)
unnamed: D68.1 (DOUT), D69.3 (DIN)
unnamed: D69.1 (DOUT), D70.3 (DIN)
unnamed: D70.1 (DOUT), D71.3 (DIN)
unnamed: D71.1 (DOUT), D72.3 (DIN)
unnamed: D72.1 (DOUT), D73.3 (DIN)
unnamed: D73.1 (DOUT), D74.3 (DIN)
unnamed: D74.1 (DOUT), D75.3 (DIN)
unnamed: D75.1 (DOUT), D76.3 (DIN)
unnamed: D76.1 (DOUT), D77.3 (DIN)
unnamed: D77.1 (DOUT), D78.3 (DIN)
unnamed: D78.1 (DOUT), D79.3 (DIN)
unnamed: D79.1 (DOUT), D80.3 (DIN)
unnamed: D80.1 (DOUT), D81.3 (DIN)
unnamed: D81.1 (DOUT), D82.3 (DIN)
unnamed: D82.1 (DOUT), D83.3 (DIN)
unnamed: D83.1 (DOUT), D84.3 (DIN)
unnamed: D84.1 (DOUT), D85.3 (DIN)
unnamed: D85.1 (DOUT), D86.3 (DIN)
unnamed: D86.1 (DOUT), D87.3 (DIN)
unnamed: D87.1 (DOUT), D88.3 (DIN)
unnamed: D88.1 (DOUT), D89.3 (DIN)
unnamed: D89.1 (DOUT), D90.3 (DIN)
unnamed: D90.1 (DOUT), D91.3 (DIN)
unnamed: D91.1 (DOUT), D92.3 (DIN)
unnamed: D92.1 (DOUT), D93.3 (DIN)
unnamed: D93.1 (DOUT), D94.3 (DIN)
unnamed: D94.1 (DOUT), D95.3 (DIN)
unnamed: D95.1 (DOUT), D96.3 (DIN)
unnamed: D96.1 (DOUT), D97.3 (DIN)
unnamed: D97.1 (DOUT), D98.3 (DIN)
unnamed: D99.1 (DOUT), D100.3 (DIN)
unnamed: D100.1 (DOUT), D101.3 (DIN)
unnamed: D101.1 (DOUT), D102.3 (DIN)
unnamed: D102.1 (DOUT), D103.3 (DIN)
unnamed: D103.1 (DOUT), D104.3 (DIN)
unnamed: D104.1 (DOUT), D105.3 (DIN)
unnamed: D105.1 (DOUT), D106.3 (DIN)
unnamed: D106.1 (DOUT), D107.3 (DIN)
unnamed: D107.1 (DOUT), D108.3 (DIN)
unnamed: D108.1 (DOUT), D109.3 (DIN)
unnamed: D109.1 (DOUT), D110.3 (DIN)
unnamed: D110.1 (DOUT), D111.3 (DIN)
unnamed: D111.1 (DOUT), D112.3 (DIN)
unnamed: D112.1 (DOUT), D113.3 (DIN)
unnamed: D113.1 (DOUT), D114.3 (DIN)
unnamed: D114.1 (DOUT), D115.3 (DIN)
unnamed: D115.1 (DOUT), D116.3 (DIN)
unnamed: D116.1 (DOUT), D117.3 (DIN)
unnamed: D117.1 (DOUT), D118.3 (DIN)
unnamed: D118.1 (DOUT), D119.3 (DIN)
unnamed: D119.1 (DOUT), D120.3 (DIN)
unnamed: D120.1 (DOUT), D121.3 (DIN)
unnamed: D121.1 (DOUT), D122.3 (DIN)
unnamed: D122.1 (DOUT), D123.3 (DIN)
unnamed: D123.1 (DOUT), D124.3 (DIN)
unnamed: D124.1 (DOUT), D125.3 (DIN)
unnamed: D125.1 (DOUT), D126.3 (DIN)
unnamed: D126.1 (DOUT), D127.3 (DIN)
unnamed: D127.1 (DOUT), D128.3 (DIN)
unnamed: D128.1 (DOUT), D129.3 (DIN)
unnamed: D129.1 (DOUT), D130.3 (DIN)
unnamed: D130.1 (DOUT), D131.3 (DIN)
unnamed: D131.1 (DOUT), D132.3 (DIN)
unnamed: D132.1 (DOUT), D133.3 (DIN)
unnamed: D133.1 (DOUT), D134.3 (DIN)
unnamed: D134.1 (DOUT), D135.3 (DIN)
unnamed: D135.1 (DOUT), D136.3 (DIN)
unnamed: D136.1 (DOUT), D137.3 (DIN)
unnamed: D137.1 (DOUT), D138.3 (DIN)
unnamed: D138.1 (DOUT), D139.3 (DIN)
unnamed: D139.1 (DOUT), D140.3 (DIN)
unnamed: D140.1 (DOUT), D141.3 (DIN)
unnamed: D141.1 (DOUT), D142.3 (DIN)
unnamed: D142.1 (DOUT), D143.3 (DIN)
unnamed: D143.1 (DOUT), D144.3 (DIN)
unnamed: D144.1 (DOUT), D145.3 (DIN)
unnamed: D145.1 (DOUT), D146.3 (DIN)
unnamed: D146.1 (DOUT), D147.3 (DIN)
unnamed: D147.1 (DOUT), D148.3 (DIN)
unnamed: D148.1 (DOUT), D149.3 (DIN)
unnamed: D149.1 (DOUT), D150.3 (DIN)
unnamed: D150.1 (DOUT), D151.3 (DIN)
unnamed: D151.1 (DOUT), D152.3 (DIN)
unnamed: D152.1 (DOUT), D153.3 (DIN)
unnamed: D153.1 (DOUT), D154.3 (DIN)
unnamed: D154.1 (DOUT), D155.3 (DIN)
unnamed: D155.1 (DOUT), D156.3 (DIN)
unnamed: D156.1 (DOUT), D157.3 (DIN)
unnamed: D157.1 (DOUT), D158.3 (DIN)
unnamed: D158.1 (DOUT), D159.3 (DIN)
unnamed: D159.1 (DOUT), D160.3 (DIN)
unnamed: D160.1 (DOUT), D161.3 (DIN)
unnamed: D161.1 (DOUT), D162.3 (DIN)
unnamed: D162.1 (DOUT), D163.3 (DIN)
unnamed: D163.1 (DOUT), D164.3 (DIN)
unnamed: D164.1 (DOUT), D165.3 (DIN)
unnamed: D165.1 (DOUT), D166.3 (DIN)
unnamed: D166.1 (DOUT), D167.3 (DIN)
unnamed: D167.1 (DOUT), D168.3 (DIN)
unnamed: D168.1 (DOUT), D169.3 (DIN)
unnamed: D169.1 (DOUT), D170.3 (DIN)
unnamed: D170.1 (DOUT), D171.3 (DIN)
unnamed: D171.1 (DOUT), D172.3 (DIN)
unnamed: D172.1 (DOUT), D173.3 (DIN)
unnamed: D173.1 (DOUT), D174.3 (DIN)
unnamed: D174.1 (DOUT), D175.3 (DIN)
unnamed: D175.1 (DOUT), D176.3 (DIN)
unnamed: D176.1 (DOUT), D177.3 (DIN)
unnamed: D177.1 (DOUT), D178.3 (DIN)
unnamed: D178.1 (DOUT), D179.3 (DIN)
unnamed: D179.1 (DOUT), D180.3 (DIN)
unnamed: D180.1 (DOUT), D181.3 (DIN)
unnamed: D181.1 (DOUT), D182.3 (DIN)
unnamed: D182.1 (DOUT), D183.3 (DIN)
unnamed: D183.1 (DOUT), D184.3 (DIN)
unnamed: D184.1 (DOUT), D185.3 (DIN)
unnamed: D185.1 (DOUT), D186.3 (DIN)
unnamed: D186.1 (DOUT), D187.3 (DIN)
unnamed: D187.1 (DOUT), D188.3 (DIN)
unnamed: D188.1 (DOUT), D189.3 (DIN)
unnamed: D189.1 (DOUT), D190.3 (DIN)
unnamed: D190.1 (DOUT), D191.3 (DIN)
unnamed: D191.1 (DOUT), D192.3 (DIN)
unnamed: D192.1 (DOUT), D193.3 (DIN)
unnamed: D193.1 (DOUT), D194.3 (DIN)
unnamed: D194.1 (DOUT), D195.3 (DIN)
unnamed: D195.1 (DOUT), D196.3 (DIN)
unnamed: D197.1 (K), L1.2
unnamed: J3.A5 (CC1), R1.1
unnamed: J3.B5 (CC2), R2.2
unnamed: L1.1, U1.5 (SW)
